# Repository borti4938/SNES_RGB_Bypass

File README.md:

# The RGB Bypass Modding Boards for the SNES

There are three versions of the modding board available. Each version differs a bit in its components according to its purpose.

Take a look into the BOM, where the components are listed. Each modding board has its own page. Take also a look into the notes provided there to ensure that you create your board according to your needs.

#### Need a PCB?
Look at OSHPark: [SNES\_RGBAmp](https://oshpark.com/shared_projects/FGz6MoI9), [SNES\_RGBAmp\_wCSYNC](https://oshpark.com/shared_projects/hMAav8Ju), [SNES\_RGBAmp\_wCSYNC\_SVid](https://oshpark.com/shared_projects/QUsZvq5m)
  
Or use any other PCB service you like :) Make sure that your PCB will be produced on a **substrate of 0.8mm or thinner** to make installation smooth and easy.

If you want to go with [PCBWay.com](http://www.pcbway.com/) (non-affiliate link), you can also use [my affiliate link](http://www.pcbway.com/setinvite.aspx?inviteid=10658) to support me. Only do that if you want that!

Thank you very much!

# Installation Notes

## 1Chip-SNES (classical big model and SNES2 (Mini/Jr.))

PCB-Version to use:  

- SNES\_RGBAmp
  * mainly for 1Chip-01/02 boards
- SNES\_RGBAmp\_wCSYNC
  * mainly for 1Chip-03 boards and for SNES Mini/SFC Jr.
  * can be used in a 1Chip-01/02 if and only if the pin 3 of the MultiAV is freed (initially CSYNC (TTL) on NTSC and 12V on PAL models)
- SNES\_RGBAmp\_wCSYNC\_SVid **[1]**
  * same as SNES\_RGBAmp\_wCSYNC just with footprints for S-Video completion in SNES2 models (Mini/Jr.)

**Note [1]**  
Do not use this board in a classical big model SNES.

### Installation

#### Preparation of the SNES Mainboard

In the big model you have to free pin 1, 2 and 4 from the MultiAV, which are the outputs of the red, green and blue component, respectively. To do so, simply

- remove R15, R16 and R17 from the SNES mainboard

In the SNES2, these pins are unused, i.e., you don't have to do anything here.

If you want to /CSYNC from the modding board you also have to ensure that pin 3 of the MultiAV is also free. In a 1Chip-03 (NTSC only) and in SNES2 models, this is the case by default. In 1Chip-01/02 boards you have to:

- NTSC systems:
  * remove R12
  * optionally also remove R9 - R11 and Q1
- PAL systems:
  * remove R28 and D1

#### Decoupling caps at the MultiAV

There are some 47pF ceramic capacitors at the MultiAV at pin 1 - 4, namely C44 (pin 1), C45 (pin 2), C46 (pin 3) and C47 (pin 4). 
There are also some footprints for 47pF ceramic capacitors on the modding board , namely C14, C24, C34 and C44.  
Make sure that you either have for each pin at the MultiAV just a single cap installed. **If you unsure, just left the footprints on the MultiAV free as these caps are optional.**

**To sum up:**

- **1Chip-01/02** versions have all capacitors C44-C47 on board. So left C14-C44 on the modding board unpopulated.
- **1Chip-03** versions does not have C46 installed. So you can put C44 onto the modding board. C44 is directly next to R43.
- **SNES2** version do not C44-C47. This version even does not have footprints for them. So assemble C14-C44 on the modding board.

#### Board installation

Solder the modding board into your SNES directly on to of the MultiAV pins.  
Make sure that you don't have (electrical) contact between SNES mainboard and your modding board. If you are unsure, simply use isolating tape.  
The modding board has to face the long side of the SNES mainboard (opposite of output direction of the MultiAV port) with the solder pads.  

Connect the solder pads as follows:

- R - red image component from S-CPUN pin156
- G - green image component from S-CPUN pin157
- B - blue image component from S-CPUN pin158
- /CS - composite sync from S-CPUN pin151 (SNES\_RGBAmp\_wCSYNC and SNES\_RGBAmp\_wCSYNC\_SVid only)
- Y - luma component from S-RGB pin17 (SNES\_RGBAmp\_wCSYNC\_SVid only)
- C - chroma component from S-RGB pin12 (SNES\_RGBAmp\_wCSYNC\_SVid)
  
Look for appropriate vias and other equivalent solder joints ;) 

You find equivalent installation guide with pictures on [RetroRGB.com](http://retrorgb.com/snes.html)
(These guides do not exploit the decoupling caps. Just C46 is mentioned for /CSYNC in 1Chip-01/02 systems, but in a wrong way.)

### Misc
  
#### Jumper J1 - Low Pass Filter of the THS7373 and THS7374   

Both ICs are supported. The THS7373 has one SD-video low pass filter (used for /CSYNC) and three HD-video filters (used for R, G and B). The THS7374 has four SD-video filters.  
At the THS7373 the HD-video LPFs can be bypassed and at the THS7374 all four SD-video filters can be bypassed (using J1).  
  
The Jumper 1 is for bypassing the internal low pass filters.
 
- leave J1 open: internal filters are NOT bypassed  
- close J1: internal filters are bypassed (not effective for the SD-video channel of the THS7373)   
  
It is not possible to set the three HD-video (THS7373) or four SD-video (THS7374) low pass filters individually!

Normally, you don't need a LPF inside your SNES output. There are just a few capture cards out there who don't have a anti aliasing filter for is ADC inputs. There you have to have the LPF turned on.

On analog devices a LPF is not needed. On professional upscaling solutions like the Framemeister and OSSC you have an anti aliasing filter prior to its ADC circuits. This means you can turn the filter of the THS7374 off.

#### Some words on TTL or 75ohm /CSYNC

Actually I was under the impression that there are modern devices out there who need TTL sync. But that's not the case - at least I'm 99% sure. For example:

- OSSC needs 75ohm csync
- Framemeister needs 75ohm csync
- All consumer TVs needs 75ohm csync

Just a month ago I realised the reason, why most people want to requests TTL csync. Just because most csync cables have a resistor in the csync wire. And on the other hand - just a few weeks after that some YouTube videos arise and show how to modify RGB cables.  
A resistor inside the cable drops down the voltage level of /CSYNC to make it compatible to 75ohm inputs

Actually, all my consoles outputs true 75ohm csync (not approximately as others do "use a resistor of something in between..."), i.e. /CSYNC has negative impulses from 0V downto -300mV.  
And I went fine with it. I can run my OSSC without any problems, a Framemeister I borrowed a few weeks ago, went run fine, too :)
I even don't have to use sync filtering... 

#### Brightness and Ghosting Issues 

##### Brightness

The S-CPUN overdrives the outputs of R, G and B. This has the effect that R', G' and B' (signals going to your TV set) have higher peak-to-peak voltage values than the standard defines. In simple word, the **brightness is to high**.

The reduce the the brightness a common choice is to increase the load on the R, G and B lines (wires coming out of the S-CPUN) to correct that. Measurements were taken [by Ultron](http://assemblergames.com/l/threads/snes-mini-rgb-measurements.53053/). Thanks for that btw.
RetroRGB summarizes the final solution:

- for the 'regular' 1Chip model: [using 750 Ohm resistors](http://retrorgb.com/snes1chip.html)
- for the SNES Mini/Jr.: [using 1.2k Ohm resistors](http://retrorgb.com/snesminipremade7314.html)

The resistors, which are soldered to the SNES mainboard, got a place on the modding PCB (R11, R21 and R31). You may want to the SMD 0603 footprints for the resistors correcting the brightness, here.

**Alternatively**, you can adapt R3 on the SNES mainboard. This is a 1.6k Ohm resistor in SMD0805 (big model) or SMD0603 (SNES2) size.
From my measurements, replacing this resistor

- by a **1.74k Ohm** resistor in a big model SNES, and
- by a **1.69k Ohm** resistor in a SNES2 (Mini/Jr.)  
  (Just an estiamtion, I hadn't had a SNES2 for measurements here, so far)

seems to be a good choice. **By replacing R3 on the SNES mainboard** you must not use the brightness correction resistors R11, R21 and R31 on the modding board.

##### Ghosting

Also some consoles have some output swing on changes of the output amplitude. These swing can be +/- 10mV to 20mV in peak-to-peak and runs over several pixels width. This results into **ghosting**.

The ghosting can be vanished by replacing C11 on the SNES mainboard by a 220nF (accuracy +/- 20% is fair enough) X5R / X7R ceramic capacitor in SMD0805 (big model) or SMD0603 (SNES2) size.
**Many thanks to [Voultar and Ste](https://shmups.system11.org/viewtopic.php?p=1282757#p1282757) for finding that out!!!**

---

## 3Chip-SNES

PCB-Version to use:  

- SNES\_RGBAmp **[3]**
  * for 3Chip-SNES boards
  * 3Chip-SNES = SNES with dedicated S-CPU, S-PPU1 and S-PPU2
- SNES\_RGBAmp\_wCSYNC
  * can be used, too, but this is not documented here. Just make sure, that you don't have another output on pin 3 of the MultiAV and find an appropriate /CSYNC source.

**Note [3]** Left the footprints for the 47pF ceramic capacitors on the modding board , namely C14, C24, C34 and C44, **unpopulated** 

**INTSTALLATION MAY DIFFER FROM MAINBOARD VERSION TO MAINBOARD VERSION!**
  
The presented installation methods here are either

- reported: I haven't done the modification by myself but it is reported to work in that way, or  
- checked: I have done the modification by myself and have measured the output with an oscilloscope.

If I have a reference url, I will give it.

### Installation
#### SNSP-CPU-01/02 (checked)
  
##### additional components needed for the SNES mainboard:
- 3x 750Ohm resistor 0805 package (0.125W, 1% tolerance should be fine)  
- 3x 1.87kOhm resistor 0805 package (0.125W, 1% tolerance should be fine)   

##### how to install:  
- remove R8, R9, R13, R14, R18, R19 and Q4, Q6, Q8 from the SNES mainboard  
- solder the three 1.87kOhm resistors to R8, R13 and R18  
- solder the three 750Ohm resistors to R9, R14 and R19  
- solder the directly beneath the MultiAV  
- connect pad 'R' with the pad where the base of Q4 was  
- connect pad 'G' with the pad where the base of Q6 was  
- connect pad 'B' with the pad where the base of Q8 was  
  
##### reference url: [German forum Circuit-Board.de](https://circuit-board.de/forum/index.php/Thread/20199-SNES-RGB-Bypass-für-PAL-3-Chip-SNES-SNSP-CPU-01-02/)
  
#### SHVC-CPU-01 (reported)

##### additional components needed for the SNES mainboard:
- 3x 750Ohm resistor 0805 package (0.125W, 1% tolerance should be fine)  
- 3x 1.87kOhm resistor 0805 package (0.125W, 1% tolerance should be fine)   
  
##### how to install:  
- cut traces for R', G' and B' right before the MultiAV (but behind C44, C45 and C47)  
- solder the three 1.87kOhm resistors to R8, R13 and R18  
- solder the three 750Ohm resistors to R9, R14 and R19  
- solder modding board to the MultiAV  
- connect pad 'R' with the point (R8,R9)  
- connect pad 'G' with the point (R13,R14)  
- connect pad 'B' with the point (R18,R19)  
  
##### reference url: [English forum AssemblerGAMES](http://assemblergames.com/l/threads/attempted-to-rgb-bypass-shvc-cpu-01-super-famicom-picture-too-bright.63581/)

#### SNS-CPU-GBM-01/02 (---)

It likely the same procedure as for the SHVC-CPU-01. Yet, I haven't tested it and it was never reported! Please keep that in mind if you decide to install the bypass board into your SNES and please report the result to me.
  
#### SNS-CPU-RGB-01/02 (---) 
  
The installation on these mainboards should be similar to the one presented for the SNS-CPU-APU-01; but it was never reported so far.  
If you do the modification (on your own risk), please report the result to me. 
  
#### SNS-CPU-APU-01 (checked) 
  
##### how to install:  
- remove R56, R57 and R58 from the SNES mainboard  
- solder modding board to the MultiAV  
- connect pad 'R' with the point (R6,R7,C6)  
- connect pad 'G' with the point (R8,R9,C7)  
- connect pad 'B' with the point (R10,R11,C8) 

##### reference url: [German forum Circuit-Board.de](https://circuit-board.de/forum/index.php/Thread/20199-SNES-RGB-Bypass-f%C3%BCr-PAL-3-Chip-SNES-SNSP-CPU-01-02/?postID=537811#post537811)

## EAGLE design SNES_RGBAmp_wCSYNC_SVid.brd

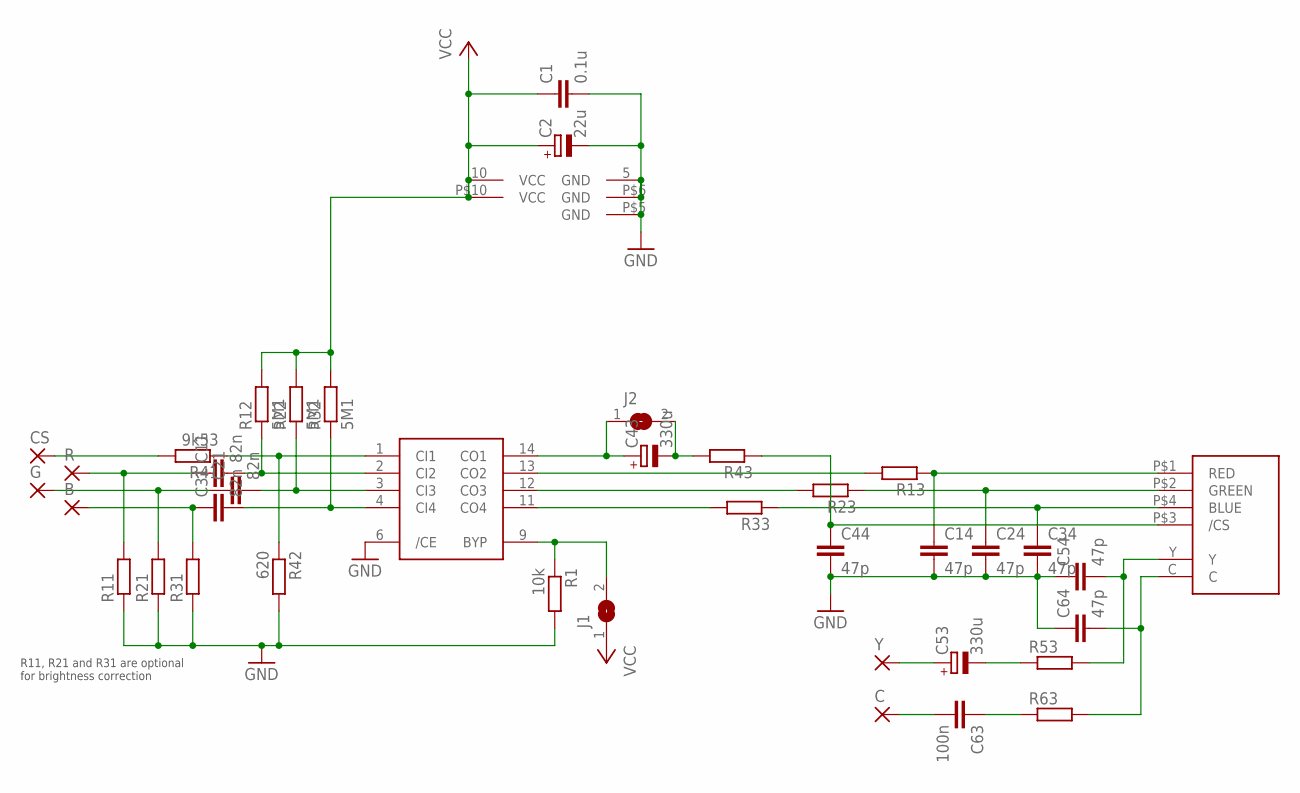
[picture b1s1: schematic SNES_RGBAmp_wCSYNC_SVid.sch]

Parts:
B: SMD2; SMD1,27-2,54
C: SMD2; SMD1,27-2,54
C1: 0.1u; C0603K
C2: 22u; SMC_B
C11, C21, C31: 82n; C0603K
C14, C24, C34, C44, C54, C64: 47p; C0603K
C43, C53: 330u; SMC_D
C63: 100n; C0603K
CS: SMD2; SMD1,27-2,54
G: SMD2; SMD1,27-2,54
J1, J2: SJ
R: SMD2; SMD1,27-2,54
R1: 10k; R0603
R11, R13, R21, R23, R31, R33, R43, R53, R63: R-EU_R0603; R0603
R12, R22, R32: 5M1; R0603
R41: 9k53; R0603
R42: 620; R0603
U1: THS7374
U$1: SNES_MULTIAV_RGBSYC
Y: SMD2; SMD1,27-2,54

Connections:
GND: C1.2, C2.-, C14.2, C24.2, C34.2, C44.2, C54.1, C64.1, R1.2, R11.1, R21.1, R31.1, R42.2, U1.5 (GND), U1.6 (/CE), U$1.P$5 (GND), U$1.P$6 (GND)
unnamed: C11.2, R12.1, U1.2 (CI2)
unnamed: C21.2, R22.1, U1.3 (CI3)
unnamed: J1.2, R1.1, U1.9 (BYP)
unnamed: C44.1, R43.1, U$1.P$3 (/CS)
unnamed: C14.1, R13.1, U$1.P$1 (RED)
unnamed: C24.1, R23.1, U$1.P$2 (GREEN)
unnamed: R23.2, U1.12 (CO3)
unnamed: R13.2, U1.13 (CO2)
unnamed: C34.1, R33.1, U$1.P$4 (BLUE)
unnamed: R41.1, R42.1, U1.1 (CI1)
unnamed: R33.2, U1.11 (CO4)
unnamed: C53.+, Y.1
unnamed: C.1, C63.2
unnamed: C11.1, R.1, R11.2
unnamed: C21.1, G.1, R21.2
unnamed: B.1, C31.1, R31.2
unnamed: CS.1, R41.2
unnamed: C43.+, J2.1, U1.14 (CO1)
unnamed: C43.-, J2.2, R43.2
unnamed: C53.-, R53.1
unnamed: C54.2, R53.2, U$1.Y
unnamed: C64.2, R63.2, U$1.C
unnamed: C63.1, R63.1
R9: C31.2, R32.1, U1.4 (CI4)
VCC: C1.1, C2.+, J1.1, R12.2, R22.2, R32.2, U1.10 (VCC), U$1.P$10 (VCC)

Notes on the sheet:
R11, R21 and R31 are optional for brightness correction

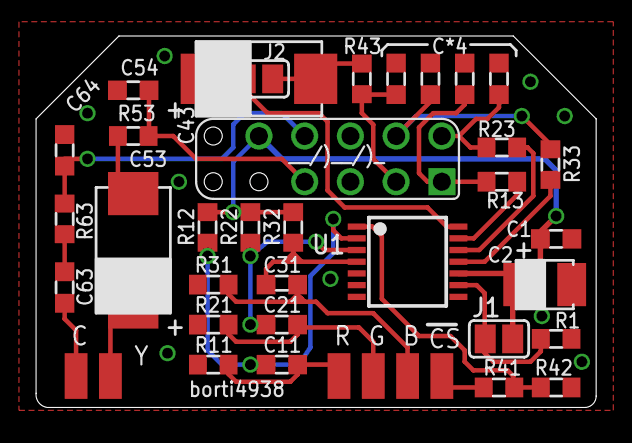
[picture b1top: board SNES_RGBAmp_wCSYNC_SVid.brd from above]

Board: 2 copper layers, 31.1 x 20.6 mm, 39 parts (0 on the bottom side), 26 nets.

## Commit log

2020-05-03 initial commit as stand alone project
2020-05-03 add license (version from origin)
2022-05-21 Update README.md
    fix (see issue #3)
